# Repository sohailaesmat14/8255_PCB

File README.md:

# 8255 Programmable Peripheral Interface (PPI) PCB

## Description

The 8255 Programmable Peripheral Interface (PPI) PCB is a custom-designed printed circuit board created by Sohaila Esmat using Eagle PCB design software. It serves as an interface between a microprocessor and peripheral devices, providing versatile I/O capabilities for digital systems.

## Features

- **Versatile I/O:** Supports three independent 8-bit I/O ports configurable as inputs or outputs.
- **Mode Selection:** Flexibility to configure each port as mode 0 (basic input/output), mode 1 (strobe input/output), or mode 2 (bi-directional bus).
- **Address Decoding:** Incorporates address decoding logic to select the appropriate device when multiple peripherals are present.
- **Eagle PCB Design:** Designed using Eagle PCB design software, ensuring reliability and compatibility with industry-standard workflows.

## Design Files

- **Schematic:** The schematic diagram of the 8255 PPI PCB is provided in Eagle `.sch` format.
- **PCB Layout:** The PCB layout design files are available in Eagle `.brd` format.
- **Gerber Files:** Gerber files for manufacturing the PCB are included for easy fabrication.

## PCB Design:

## Usage

1. **Customization:** Modify the design to suit your specific project requirements, such as integrating additional peripherals or altering the address decoding scheme.
2. **Fabrication:** Use the provided Gerber files to manufacture the PCB according to the design specifications.
3. **Integration:** Incorporate the 8255 PPI PCB into your digital electronics project, connecting it to the microprocessor and peripheral devices as needed.
4. **Testing:** Validate the functionality of the PCB by testing its I/O capabilities and ensuring proper address decoding in your system.

## Author

- **Sohaila Esmat:** [LinkedIn](https://www.linkedin.com/in/sohailaesmat/)

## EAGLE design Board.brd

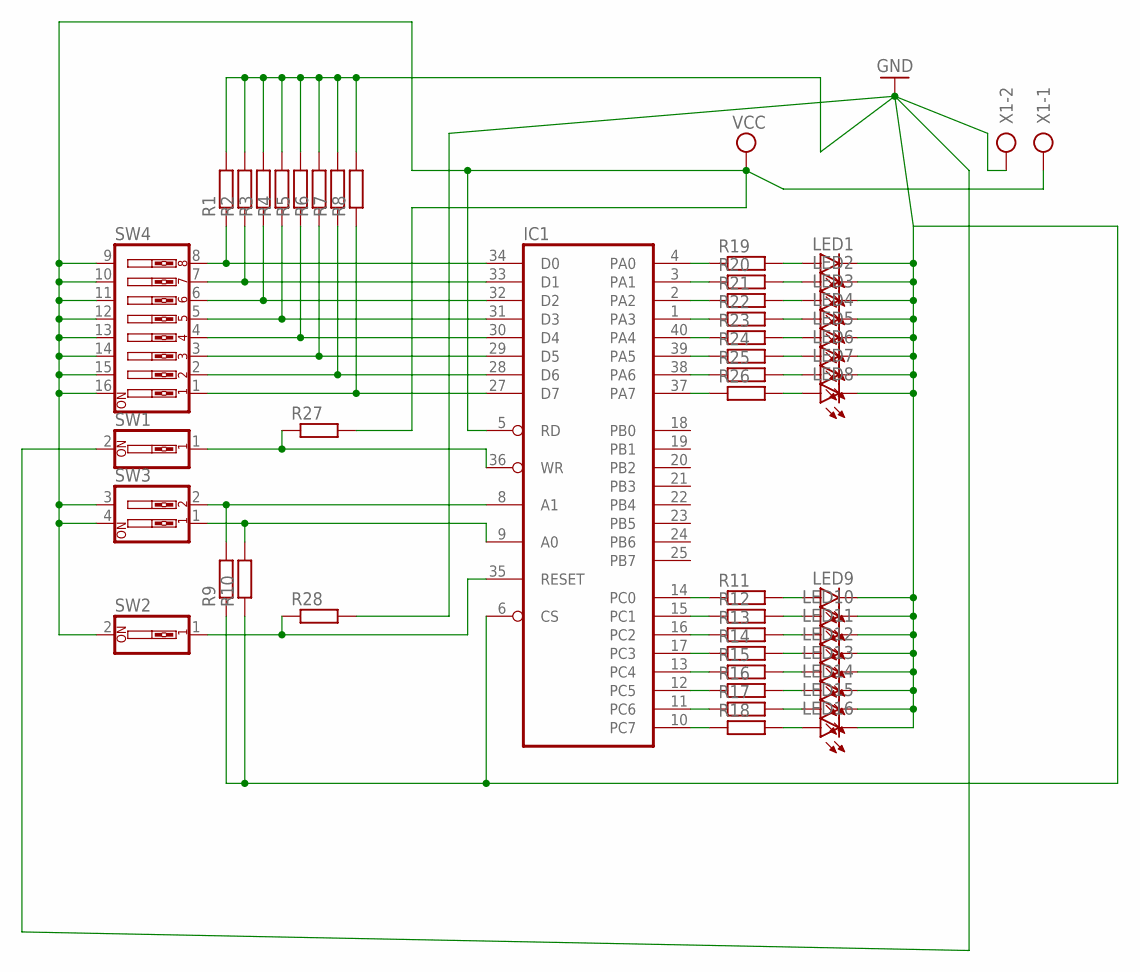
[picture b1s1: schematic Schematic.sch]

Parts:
IC1: 8255A; DIL40
LED1, LED2, LED3, LED4, LED5, LED6, LED7, LED8, LED9, LED10, LED11, LED12, LED13, LED14, LED15, LED16: LED5MM
R1, R2, R3, R4, R5, R6, R7, R8, R9, R10, R11, R12, R13, R14, R15, R16, R17, R18, R19, R20, R21, R22, R23, R24, R25, R26, R27, R28: R-EU_0207/10; 0207/10
SW1, SW2: SW_DIP-1; EDG-01
SW3: SW_DIP-2; EDG-02
SW4: SW_DIP-8; EDG-08
X1: AK500/2

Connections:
GND: IC1.6 (CS), IC1.7 (GND), LED1.K (C), LED2.K (C), LED3.K (C), LED4.K (C), LED5.K (C), LED6.K (C), LED7.K (C), LED8.K (C), LED9.K (C), LED10.K (C), LED11.K (C), LED12.K (C), LED13.K (C), LED14.K (C), LED15.K (C), LED16.K (C), R1.2, R2.2, R3.2, R4.2, R5.2, R6.2, R7.2, R8.2, R9.1, R10.1, R28.2, SW1.2, X1.2
unnamed: IC1.34 (D0), R1.1, SW4.8
unnamed: IC1.33 (D1), R2.1, SW4.7
unnamed: IC1.32 (D2), R3.1, SW4.6
unnamed: IC1.31 (D3), R4.1, SW4.5
unnamed: IC1.30 (D4), R5.1, SW4.4
unnamed: IC1.29 (D5), R6.1, SW4.3
unnamed: IC1.28 (D6), R7.1, SW4.2
unnamed: IC1.27 (D7), R8.1, SW4.1
unnamed: IC1.8 (A1), R9.2, SW3.2
unnamed: IC1.9 (A0), R10.2, SW3.1
unnamed: IC1.4 (PA0), R19.1
unnamed: LED1.A, R19.2
unnamed: LED2.A, R20.2
unnamed: LED3.A, R21.2
unnamed: LED4.A, R22.2
unnamed: LED5.A, R23.2
unnamed: LED6.A, R24.2
unnamed: LED7.A, R25.2
unnamed: LED8.A, R26.2
unnamed: IC1.37 (PA7), R26.1
unnamed: IC1.38 (PA6), R25.1
unnamed: IC1.39 (PA5), R24.1
unnamed: IC1.40 (PA4), R23.1
unnamed: IC1.1 (PA3), R22.1
unnamed: IC1.2 (PA2), R21.1
unnamed: IC1.3 (PA1), R20.1
unnamed: IC1.14 (PC0), R11.1
unnamed: IC1.15 (PC1), R12.1
unnamed: IC1.16 (PC2), R13.1
unnamed: IC1.17 (PC3), R14.1
unnamed: IC1.13 (PC4), R15.1
unnamed: IC1.12 (PC5), R16.1
unnamed: IC1.11 (PC6), R17.1
unnamed: IC1.10 (PC7), R18.1
unnamed: LED16.A, R18.2
unnamed: LED15.A, R17.2
unnamed: LED14.A, R16.2
unnamed: LED13.A, R15.2
unnamed: LED12.A, R14.2
unnamed: LED11.A, R13.2
unnamed: LED10.A, R12.2
unnamed: LED9.A, R11.2
unnamed: IC1.35 (RESET), R28.1, SW2.1
unnamed: IC1.36 (WR), R27.1, SW1.1
VCC: IC1.5 (RD), IC1.26 (VCC), R27.2, SW2.2, SW3.3, SW3.4, SW4.9, SW4.10, SW4.11, SW4.12, SW4.13, SW4.14, SW4.15, SW4.16, X1.1

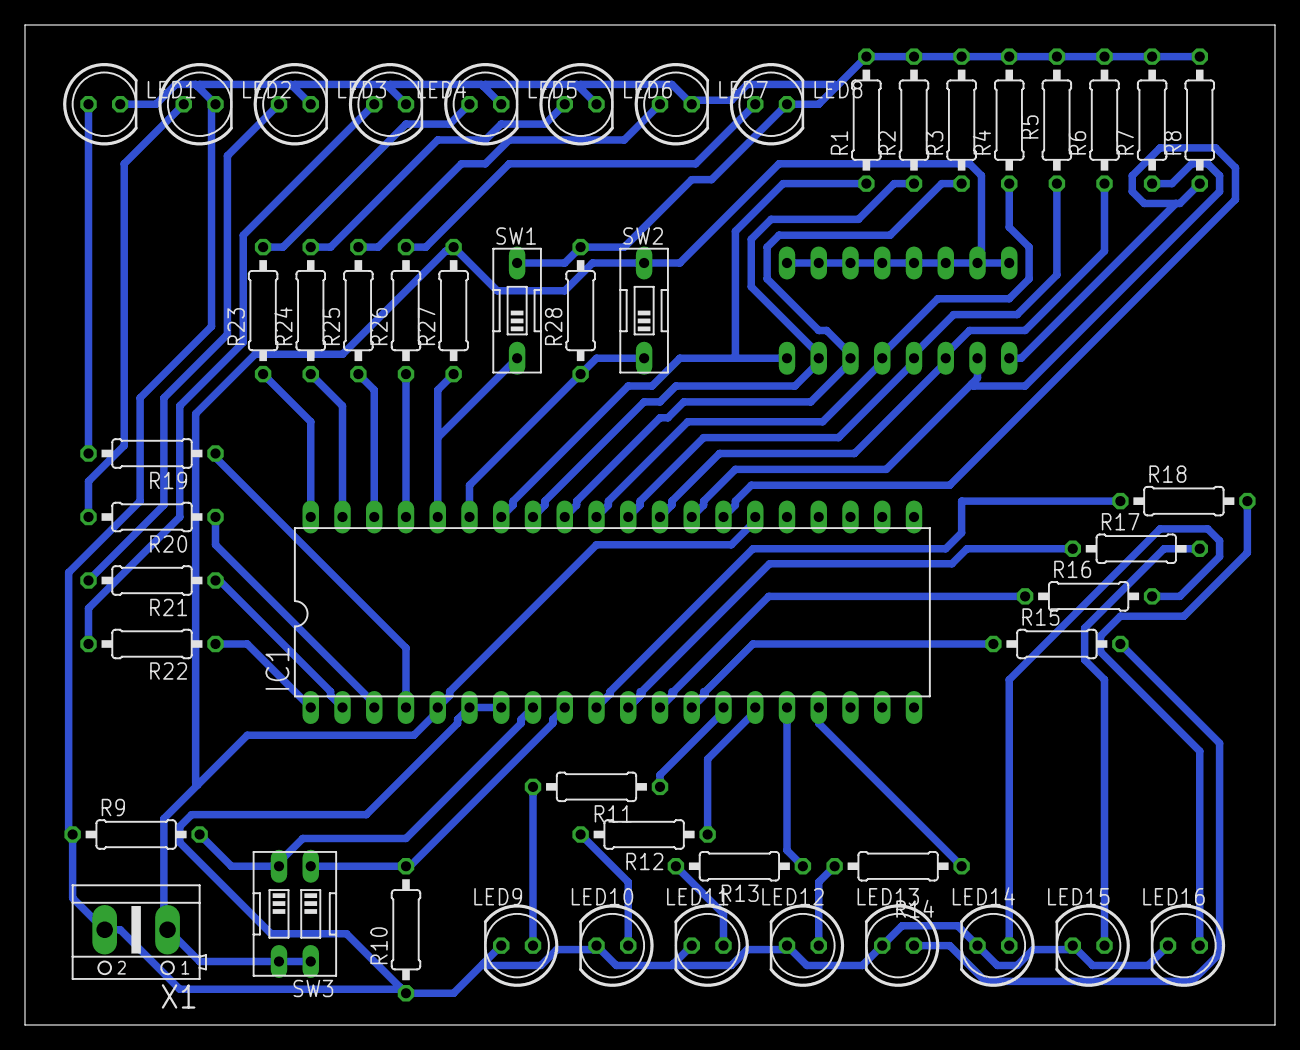
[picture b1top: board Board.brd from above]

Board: 2 copper layers, 100.0 x 80.0 mm, 50 parts (1 on the bottom side), 46 nets.
